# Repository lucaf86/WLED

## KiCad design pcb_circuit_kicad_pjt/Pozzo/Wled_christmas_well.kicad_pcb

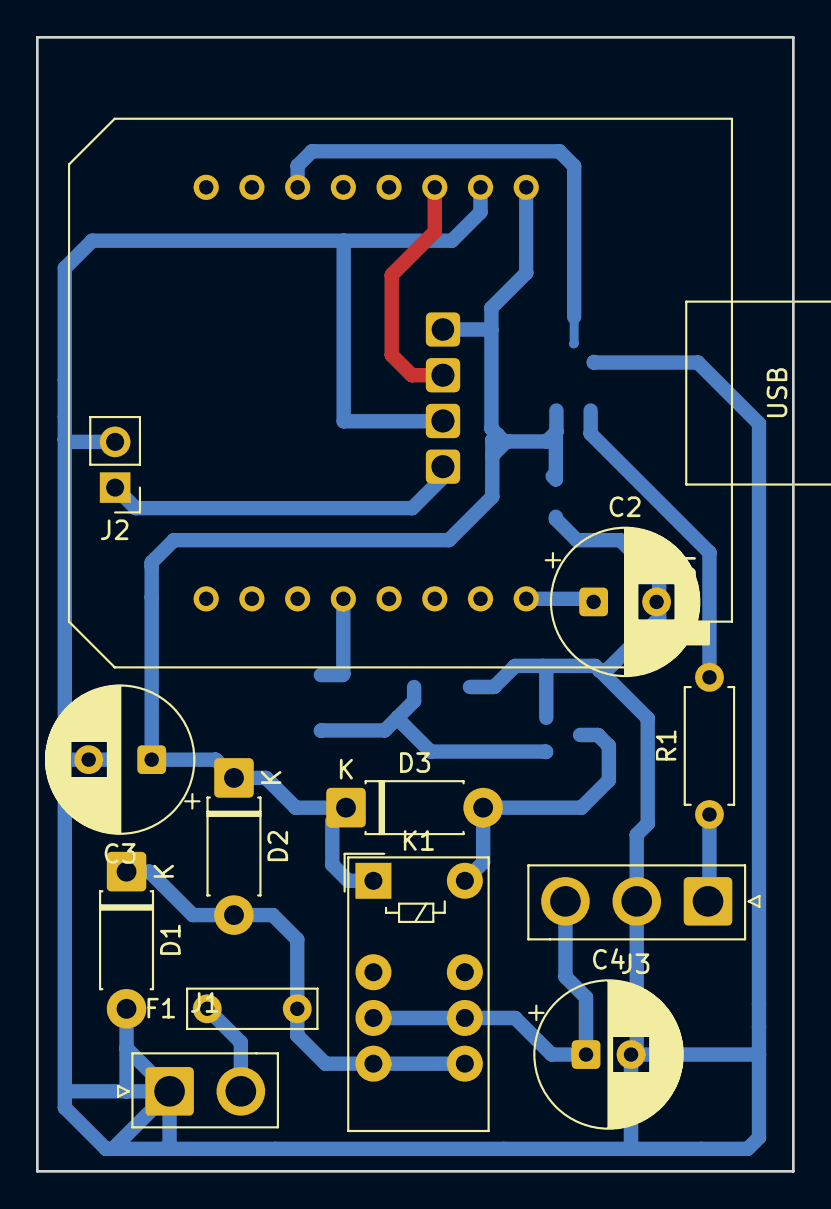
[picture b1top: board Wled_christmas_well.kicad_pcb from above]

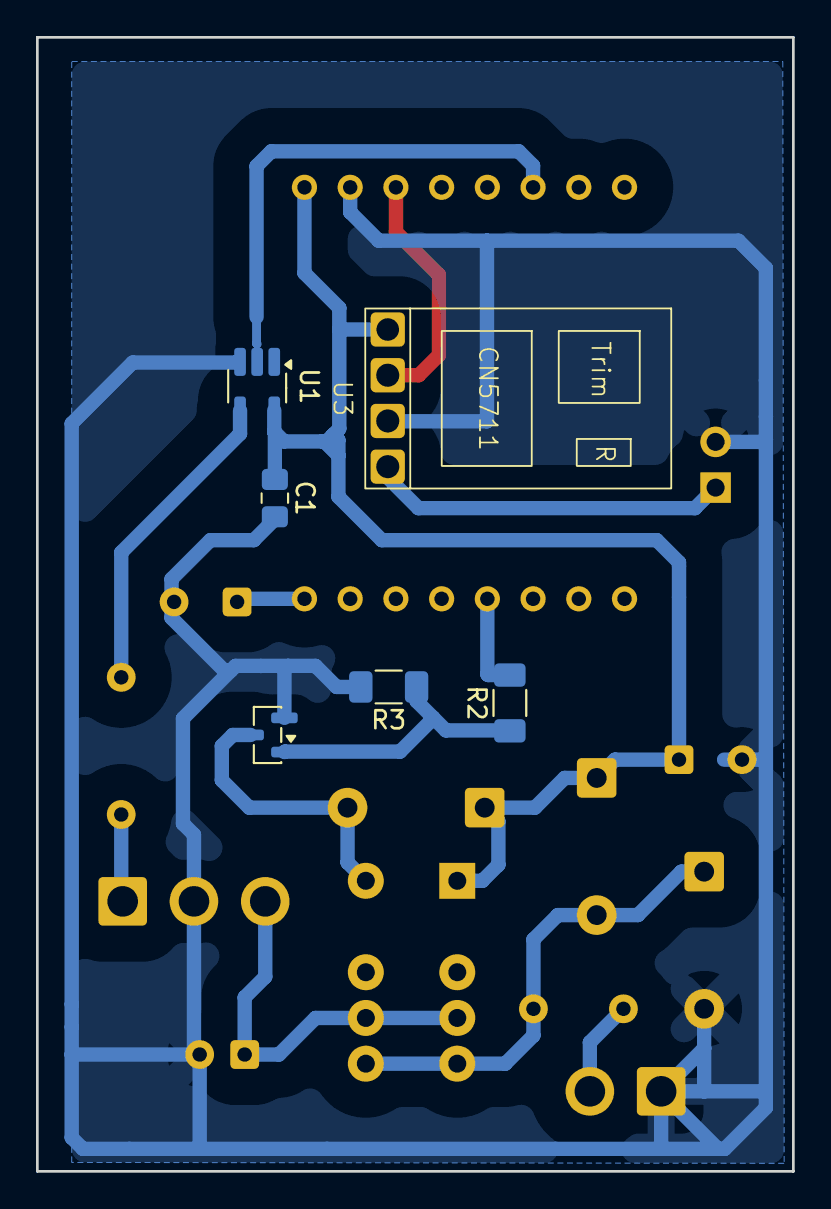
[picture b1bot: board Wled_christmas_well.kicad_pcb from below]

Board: 2 copper layers, 42.0 x 63.0 mm, 19 parts (6 on the bottom side), 14 nets.

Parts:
C1: 0.1uF; C_0805_2012Metric_Pad1.18x1.45mm_HandSolder
C2, C3: 470uF; CP_Radial_D8.0mm_P3.50mm
C4: 820uF; CP_Radial_D8.0mm_P2.50mm
D1: 1N5819 (or SK36A); D_DO-41_SOD81_P7.62mm_Horizontal
D2: 1N5819; D_DO-41_SOD81_P7.62mm_Horizontal
D3: D; D_DO-41_SOD81_P7.62mm_Horizontal
F1: Polyfuse 0.75A; C_Rect_L7.0mm_W2.0mm_P5.00mm
J1: Screw_Terminal_01x02; JST_VH_B2P-VH-B_1x02_P3.96mm_Vertical
J2: Conn_01x02; PinHeader_1x02_P2.54mm_Vertical
J3: Conn_01x03; JST_VH_B3P-VH-B_1x03_P3.96mm_Vertical
K1: G6S-2 5V; Relay_DPDT_Omron_G6S-2
Q1: SI2306; SOT-23
R1: 220 (100-500 ohm); R_Axial_DIN0207_L6.3mm_D2.5mm_P7.62mm_Horizontal
R2: 120; R_1206_3216Metric_Pad1.30x1.75mm_HandSolder
R3: 10k; R_1206_3216Metric_Pad1.30x1.75mm_HandSolder
U1: 74LVC1G17; SOT-23-5_HandSoldering
U2: mini_esp32; ESP32_mini_w_8266_pinout_only
U3: LD06AJSA; Untitled

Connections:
+5V: C1.1, C3.1, D2.1 (K), D3.1 (K), K1.1, U1.5 (VCC), U2.35 (VCC_(USB)), U3.1 (VI)
+5V_LED: C4.1, J3.3, K1.4, K1.9
GND: C1.2, C2.2, C3.2, C4.2, D1.2 (A), J1.1, J2.2, J3.2, Q1.2 (S), R3.2, U1.3 (GND), U2.33 (GND), U3.3 (GND)
LED1: U1.2, U2.25 (IO_22/D1/SCL)
LED2: U2.31 (IO_16/D4), U3.2 (CE)
LED_COB_OUT_2: J2.1, U3.4 (LED)
LED_STRING_OUT_1: J3.1, R1.1
unnamed: D3.2 (A), K1.12, Q1.3 (D)
unnamed: F1.2, J1.2
unnamed: Q1.1 (G), R2.1, R3.1
unnamed: R1.2, U1.4
unnamed: C2.1, U2.16 (3V3)
RELAY: R2.2, U2.8 (IO_18/D5)
VDC: D1.1 (K), D2.2 (A), F1.1, K1.5, K1.8

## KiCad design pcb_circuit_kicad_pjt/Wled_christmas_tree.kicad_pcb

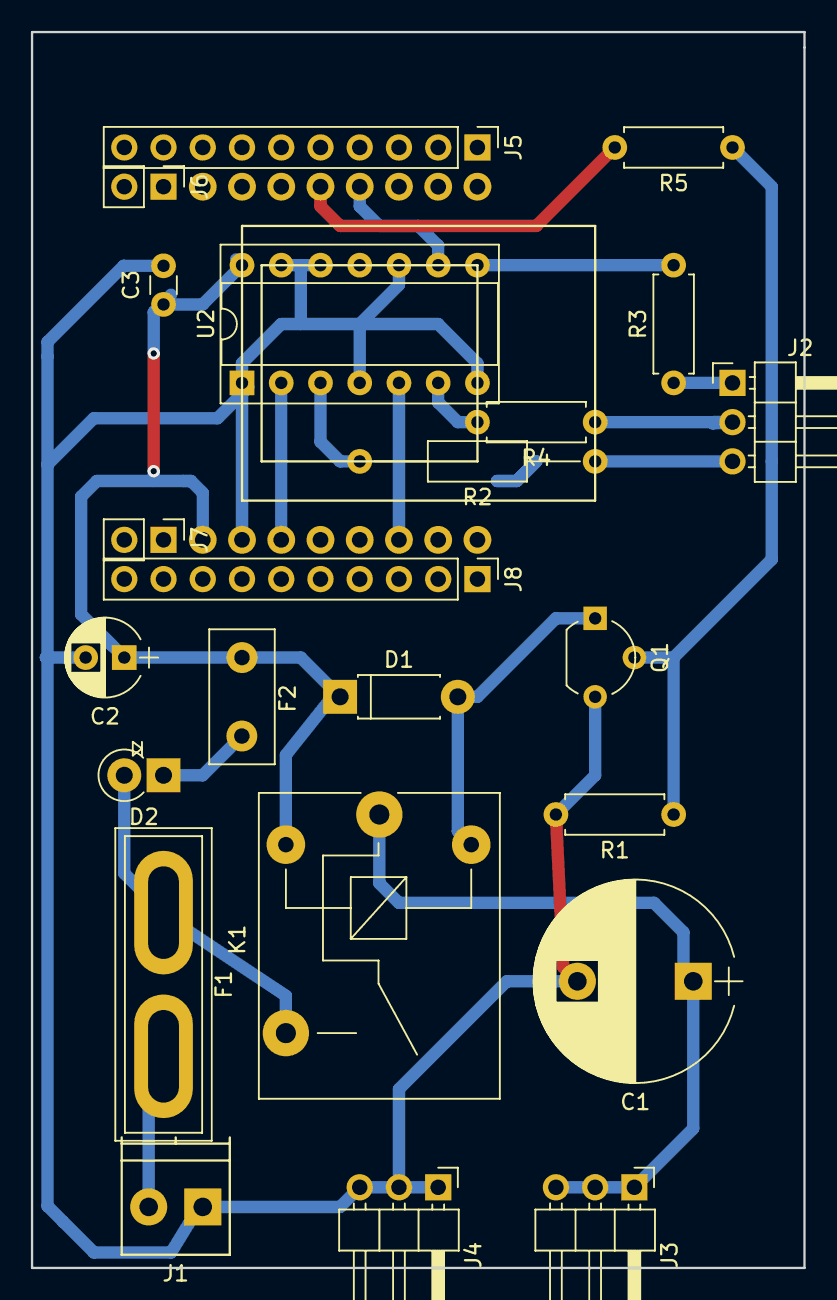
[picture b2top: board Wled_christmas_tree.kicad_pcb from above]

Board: 2 copper layers, 50.0 x 80.0 mm, 24 parts (1 on the bottom side), 18 nets.

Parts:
C1: 1000uF; CP_Radial_D13.0mm_P7.50mm
C2: CP; CP_Radial_D5.0mm_P2.50mm
C3: 0.1uF for SN74AHCT125; C_Disc_D3.0mm_W1.6mm_P2.50mm
D1: D; D_DO-41_SOD81_P7.62mm_Horizontal
D2: 1N5817; D_DO-41_SOD81_P2.54mm_Vertical_KathodeUp
F1: DC car Fuse 3A; BladeFuse-CarType
F2: Polyfuse 0.5A; Fuse_TE5_Littlefuse-395Series
J1: Screw_Terminal_01x02; TerminalBlock_Phoenix_PT-3.5mm_2pol
J2, J3, J4: Conn_01x03; Pin_Header_Angled_1x03_Pitch2.54mm
J5: Extra_pin_esp32_1; Pin_Header_Straight_1x10_Pitch2.54mm
J6, J7: Conn_01x02; Pin_Header_Straight_1x02_Pitch2.54mm
J8: Extra_pin_esp32_2; Pin_Header_Straight_1x10_Pitch2.54mm
K1: JS1a-5V; Relay_SPST_SANYOU_SRD_Series_Form_A
Q1: 2N2222; TO-92_Molded_Wide
R1: 10K; R_Axial_DIN0207_L6.3mm_D2.5mm_P7.62mm_Horizontal
R2: 100 - 500 ohm; R_Axial_DIN0207_L6.3mm_D2.5mm_P15.24mm_Horizontal
R3, R4: 100 - 500 ohm; R_Axial_DIN0207_L6.3mm_D2.5mm_P7.62mm_Horizontal
R5: 1K; R_Axial_DIN0207_L6.3mm_D2.5mm_P7.62mm_Horizontal
U1: WeMos_mini; D1_mini_board
U2: SN74AHCT125; DIP-14_W7.62mm_Socket

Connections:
+5V: C2.1, C3.1, D1.1, F2.1, K1.5, U1.1, U2.14
+5V_LED: C1.1, J3.1, J3.2, J3.3, K1.1
+VDC: D2.2, F1.1, K1.4
GND: C1.2, C2.2, C3.2, J1.1, J4.1, J4.2, J4.3, Q1.3, R1.2, U1.2, U2.1, U2.4, U2.7, U2.10, U2.12, U2.13
LED1: U1.3, U2.2
LED2: U1.12, U2.9
LED3: U1.6, U2.5
LED_OUT_1: J2.3, R2.1
LED_OUT_2: J2.1, R3.1
LED_OUT_3: J2.2, R4.1
unnamed: D1.2, K1.2, Q1.1
unnamed: D2.1, F2.2
unnamed: F1.2, J1.2
unnamed: Q1.2, R1.1, R5.1
unnamed: R2.2, U2.3
unnamed: R3.2, U2.8
unnamed: R4.2, U2.6
RELAY: R5.2, U1.13

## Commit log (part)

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2020-11-14 merged multiple led strip control from https://github.com/peacepenguin/WLED (issue https://github.com/Aircoookie/WLED/issues/104)
    This build is for wemos D1 (aka esp8266):
    - disabled Hue Synch -D WLED_DISABLE_HUESYNC
    - disabled IR -D WLED_DISABLE_INFRARED
    - disabled mqtt -D WLED_DISABLE_MQTT
    - button pin on gpio 0 (D3)
    - relay pin on gpio 12 (D6)
2020-11-14 dummy
2020-11-20 - switched pin 3 (RX) with 14 (D5) used in bitBang mode - disabled ADALIGHT feature since not needed - add some new effects
2020-11-22 disabled WLED_ENABLE_LOXONE feature
2020-11-22 four color fe update
2020-11-23 - added esp8266_multistrip usermod (see README.md for info) - reverted wled00/NpbWrapper.h (customization for multistrip mover in usermod) - added d1_mini_multistrip env in PIO .ini. Set as default
2020-11-26 removed linear blend on palette in lake effect rewrite fade_in_out_alternate effect to use different segments (4 segment, 1 pixel with 3 spaces for each segment)
2020-11-26 rebuild UI with node js after fetching the pull request
2020-12-08 disabled unwanted features try to prevent wdt reset with extra yield (seems not to avoid crash, just delay it) try to reduce frame rate
2020-12-09 disabled unwanted features tested without led attached, 14h uptime
2020-12-10 attemp to fix json acces causing possible crashes
2020-12-13 -add json backup -add flash dump of old firmware installed -update esp8266_multistrip/NpbWrapper.h usermod with latest master changes. Merged CanShow() from esp32 usermod pull request -avoid updating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
2020-12-13 add new json backup
2020-12-14 fixed Alexa device discovery. Unique id used by Wled is 7 character but it must be 12 characters long! Applied the same calculation used in Fauxmo lib https://github.com/vintlabs/fauxmoESP
2020-12-15 improve check on alexa discovery
2020-12-15 try to build with develop branch of esp8266 core
2020-12-15 set correct default env
2020-12-15 add firmware and json of build with dev core and updated lib
2020-12-16 add 'alexaDiscover' json entry in cfg.json, used to enable/disable UDP multicast server used for Alexa device discovery. When alexa emulation is active, if alexaDiscover is set to true the device is 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
    cfg.json file must be edit by hand at http://device-IP/edit
    1-set to:
    "va":{"alexa":true,"alexaDiscover":true,"macros":[0,0]}
    2-Reboot
    3-Search and add Alexa device with app
    4-disable search by editing json
2020-12-16 -removed md5 calculation, now uniqueId is just the first part of the MAC followed by the device id (aabbccddeeii) -removed decodeLightId() call since no more needed
2020-12-17 -avoid clock overlay and e131 cal completely when feature not compiled -disable all UDP connection other than ntp (and alexa) when wifi STA connectded (WLED_DISABLE_UDP_IN_WIFI_STA)
2020-12-18 check error on json read restored UDP servers in build
2020-12-21 -revert to official arduino core .extended MIN_SHOW_DELAY to match reduced framerate timing -disable wifi autoreconnect -add debug code for custom show
2020-12-22 revert alexa discovery disable in json (code under ifdef)
2020-12-22 esp32 multistrip branch and initial setup
2020-12-23 esp32 firmware and json backup
2020-12-23 update cfg json with correct alexa off preset
2021-01-17 add christmas tree circuit and pcb kicad project
2021-10-03 moved custom config in platformio_override.ini
2021-11-14 json backup for new esp32 firmware with dynamic multistrip in cfg menu
2021-11-27 backup new json
2021-11-27 new firmware for esp32
2021-11-29 fixed cfg in platformio_override.ini enabled philips hueu code (without it Alexa won't find the device, don't know why)
2021-12-21 add Lantern platform and json
2021-12-27 backup json config
2022-11-04 restore albero_esp32_multistrip profile
2022-11-04 reintegrate custom effects on WLED v14
2023-09-29 merging custom effects and adaptation to v0.14
    Squashed commit of the following:
    commit 15d6d3e6a5467d7fdf9f92d41e97997a32e39023
    Merge: 5e44449e 102a28ae
    Author: fusaril <luca.fusari@azcom.it>
    Date: Tue Nov 8 09:46:35 2022 +0100
    Merge tag 'v0.13.3' into esp32_multistrip
2023-09-29 update schematic for esp32
2023-09-29 restore deleted file
2023-10-01 backup of 2022
2023-10-02 wled v0.14 ugrade on september 2023, backup new firmaware, cfg and preset json
2023-10-20 set default env
2025-01-08 backup pozzo natale 2024, singola stringa da 10m divisa in due profili, uno per alberello e uno per legna, collegata al gpio18 a cui è stata abbassata la resistenza in serie al canale dati per interf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
2025-11-03 fix platform io cfg
2025-11-14 restore correct pdf of the schematic
2025-11-14 fix env after merging v0.15.1
2025-12-01 env per pozzo
2025-12-01 create subfolder for pcb files
2025-12-03 cleanup
2025-12-03 fix configuration and add new one for "pozzo"
2025-12-03 pcb pozzo
2026-01-07 backup pozzo 2025 con sk6812 rgbw
